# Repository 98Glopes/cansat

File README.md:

# cansat
1 Competição de Cansat TecnoFacens - Projeto nanosatélite Balão Magico

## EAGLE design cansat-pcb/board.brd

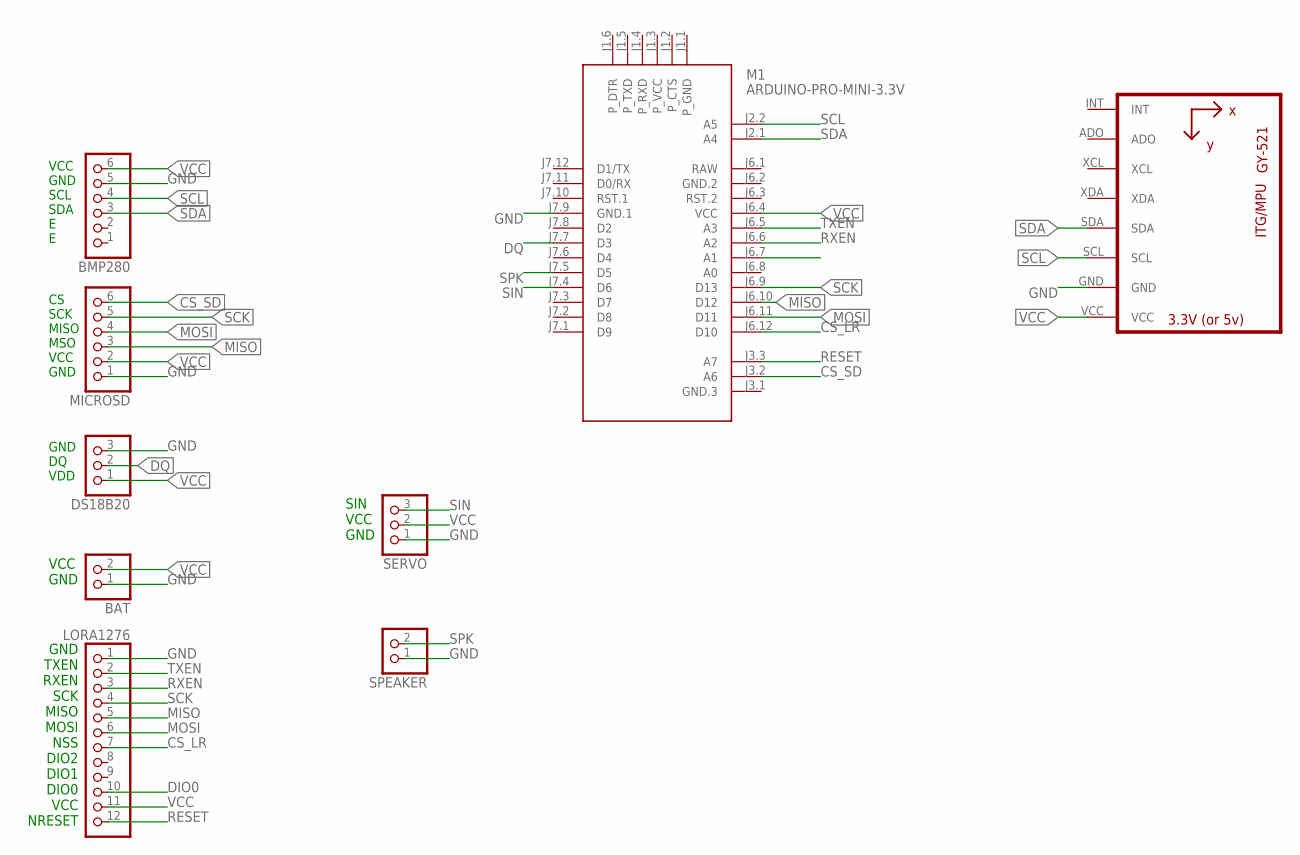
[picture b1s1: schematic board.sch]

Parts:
BAT: PINHD-1X2; 1X02
BMP280: PINHD-1X6; 1X06
DS18B20: PINHD-1X3; 1X03
LORA1276: PINHD-1X12; 1X12
M1: ARDUINO-PRO-MINI-3.3V; ARDUINO-PRO-MINI
MICROSD: PINHD-1X6; 1X06
SERVO: PINHD-1X3; 1X03
SPEAKER: PINHD-1X2; 1X02
U1: GY-521MPU6050; GY-521

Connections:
CS_LR: LORA1276.7, M1.J6.12 (D10)
CS_SD: M1.J3.2 (A6), MICROSD.6
DIO0: LORA1276.10, M1.J6.7 (A1)
DQ: DS18B20.2, M1.J7.7 (D3)
GND: BAT.1, BMP280.5, DS18B20.3, LORA1276.1, M1.J7.9 (GND.1), MICROSD.1, SERVO.1, SPEAKER.1, U1.GND
GND.2: M1.J6.2 (GND.2)
MISO: LORA1276.5, M1.J6.10 (D12), MICROSD.3
MOSI: LORA1276.6, M1.J6.11 (D11), MICROSD.4
RAW: M1.J6.1 (RAW)
RESET: LORA1276.12, M1.J3.3 (A7)
RXEN: LORA1276.3, M1.J6.6 (A2)
SCK: LORA1276.4, M1.J6.9 (D13), MICROSD.5
SCL: BMP280.4, M1.J2.2 (A5), U1.SCL
SDA: BMP280.3, M1.J2.1 (A4), U1.SDA
SIN: M1.J7.4 (D6), SERVO.3
SPK: M1.J7.5 (D5), SPEAKER.2
TXEN: LORA1276.2, M1.J6.5 (A3)
VCC: BAT.2, BMP280.6, DS18B20.1, LORA1276.11, M1.J6.4 (VCC), MICROSD.2, SERVO.2, U1.VCC

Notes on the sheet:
VCC GND SCL SDA E E
CS SCK MISO MSO VCC GND
GND DQ VDD
VCC GND
GND TXEN RXEN SCK MISO MOSI NSS DIO2 DIO1 DIO0 VCC NRESET
SIN VCC GND

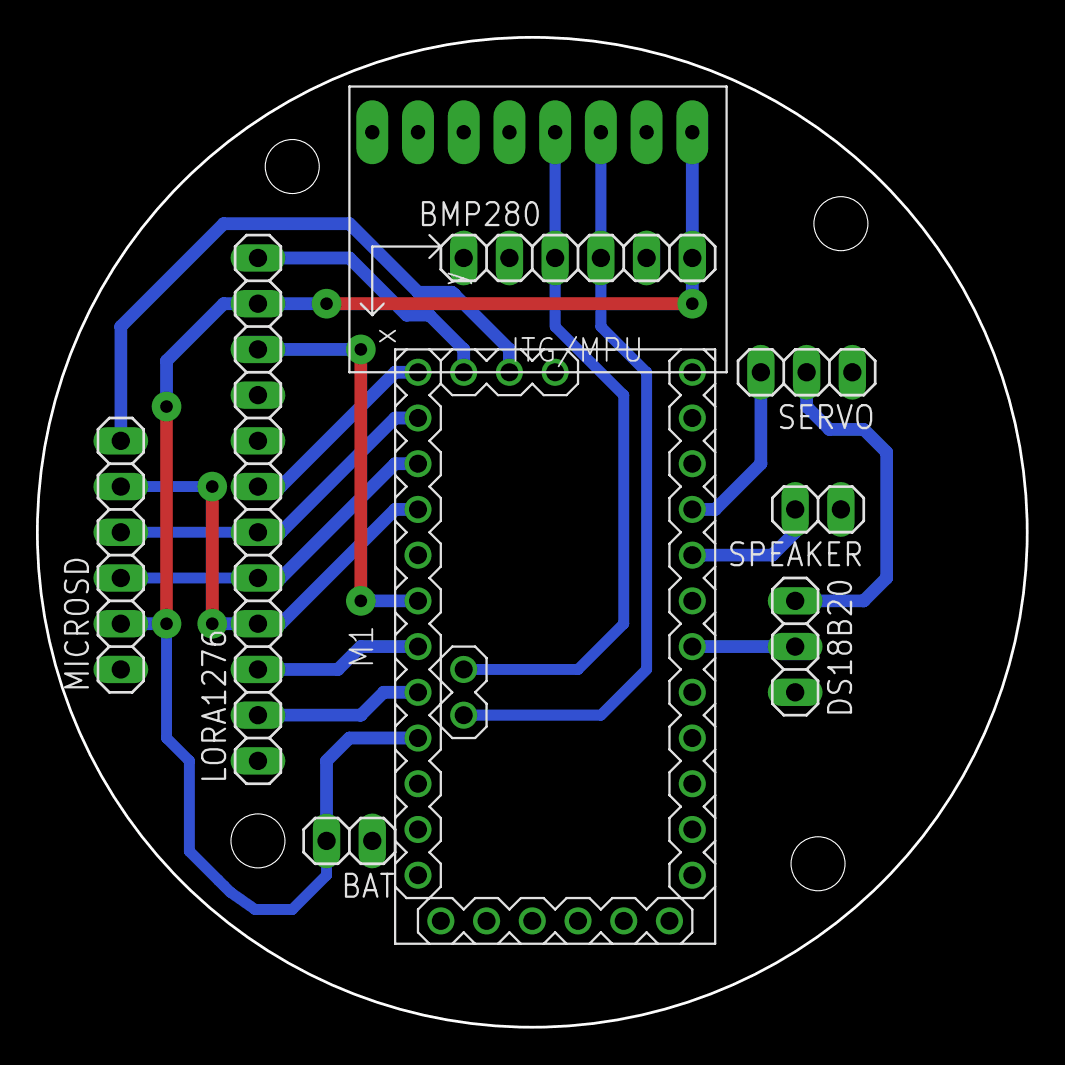
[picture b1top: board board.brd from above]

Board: 2 copper layers, 55.0 x 55.0 mm, 9 parts (0 on the bottom side), 16 nets.

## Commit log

2019-09-28 Adcionado pcb
2019-10-01 3d-model
2020-01-15 backup

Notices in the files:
parts and their libraries:
diy-modules: Released under the Creative Commons Attribution 4.0 International License: http://creativecommons.org/licenses/by/4.0
